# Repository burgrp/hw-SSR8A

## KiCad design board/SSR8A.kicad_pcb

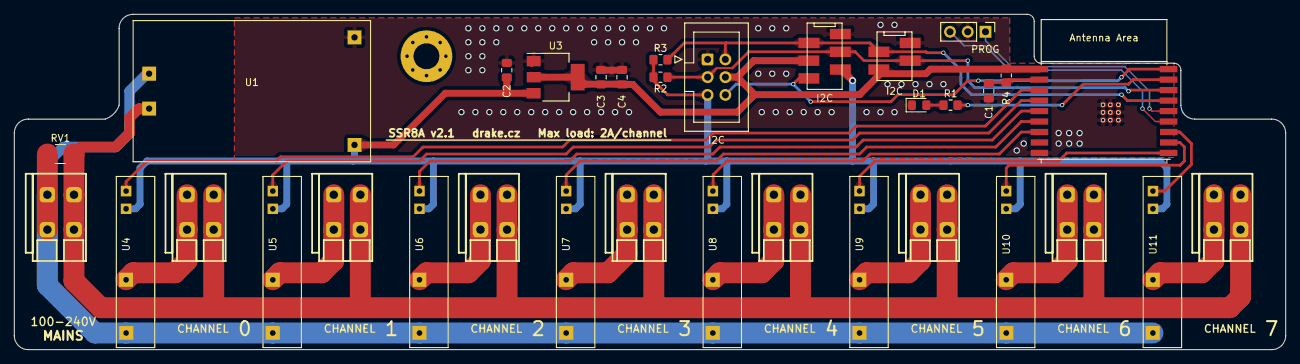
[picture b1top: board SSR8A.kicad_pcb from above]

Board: 2 copper layers, 182.0 x 48.0 mm, 35 parts (0 on the bottom side), 29 nets.

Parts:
C1: 1u; C_0805_2012Metric_Pad1.18x1.45mm_HandSolder
C2: 10u; C_0805_2012Metric_Pad1.18x1.45mm_HandSolder
C3, C4: 47u; C_0805_2012Metric_Pad1.18x1.45mm_HandSolder
D1: LED; LED_0805_2012Metric_Pad1.15x1.40mm_HandSolder
H1: MountingHole; MountingHole_3.7mm_Pad_Via
IN1: Conn_01x02; DG235-3.81-02P
J1: PROG; PinHeader_1x03_P2.54mm_Vertical
J2, J3, J4, J5, J6, J7, J8, J9: Conn_01x02; DG235-3.81-02P
R1: 270R; R_0805_2012Metric_Pad1.20x1.40mm_HandSolder
R2, R3: 4k7; R_0805_2012Metric_Pad1.20x1.40mm_HandSolder
R4: 10k; R_0805_2012Metric_Pad1.20x1.40mm_HandSolder
RV1: B72650M251K72; R_1210_3225Metric_Pad1.30x2.65mm_HandSolder
U1: HLK-PM01
U2: ESP32-C3-WROOM-02; ESP32-C3-WROOM-02 Handsolder
U3: LM1117-3.3; SOT-223-3_TabPin2
U4, U5, U6, U7, U8, U9, U10, U11: G3MB-SSR
X1: I2C; Micro-Match-FOB-4
X2: I2C; Micro-Match-FOB-6
X3: I2C; IDC-Header_2x03_P2.54mm_Vertical

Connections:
+3V3: C3.1, C4.1, R4.1, U2.1 (3V3), U3.2 (VO), X1.4 (3V3), X2.4 (3V3), X3.4 (3V3)
+5V: C2.1, R2.2, R3.1, U1.4 (OUT+), U3.3 (VI), U4.3 (IN+), U5.3 (IN+), U6.3 (IN+), U7.3 (IN+), U8.3 (IN+), U9.3 (IN+), U10.3 (IN+), U11.3 (IN+), X2.5 (5V), X3.5 (5V)
/ALERT: U2.18 (GPIO0/ADC1_CH0/XTAL_32K_P), X2.6 (ALERT), X3.6 (ALERT)
/LED: R1.2, U2.17 (GPIO1/ADC1_CH1/XTAL_32K_N)
/MAINS-L: IN1.1, RV1.1, U1.1 (LINE1), U4.1 (LOAD1), U5.1 (LOAD1), U6.1 (LOAD1), U7.1 (LOAD1), U8.1 (LOAD1), U9.1 (LOAD1), U10.1 (LOAD1), U11.1 (LOAD1)
/MAINS-N: IN1.2, J2.2, J3.2, J4.2, J5.2, J6.2, J7.2, J8.2, J9.2, RV1.2, U1.2 (LINE2)
/SCL: R3.2, U2.15 (GPIO3/ADC1_CH3), X1.2 (SCL), X2.2 (SCL), X3.2 (SCL)
/SDA: R2.1, U2.16 (GPIO2/ADC1_CH2), X1.3 (SDA), X2.3 (SDA), X3.3 (SDA)
/USB_D+: J1.1, U2.14 (GPIO19/USB_D+)
/USB_D-: J1.3, U2.13 (GPIO18/USB_D-)
//CH0: U2.3 (GPIO4/ADC1_CH4), U4.4 (IN-)
//CH1: U2.4 (GPIO5/ADC2_CH0), U5.4 (IN-)
//CH2: U2.5 (GPIO6), U6.4 (IN-)
//CH3: U2.6 (GPIO7), U7.4 (IN-)
//CH4: U2.7 (GPIO8), U8.4 (IN-)
//CH5: U2.10 (GPIO10), U9.4 (IN-)
//CH6: U2.11 (GPIO20/U0RXD), U10.4 (IN-)
//CH7: U2.12 (GPIO21/U0TXD), U11.4 (IN-)
GND: C1.2, C2.2, C3.2, C4.2, D1.1 (K), J1.2, U1.3 (OUT-), U2.9 (GND), U2.19 (GND), U3.1 (GND), X1.1 (GND), X2.1 (GND), X3.1 (GND)
unnamed: D1.2 (A), R1.1
unnamed: J2.1, U4.2 (LOAD2)
unnamed: J3.1, U5.2 (LOAD2)
unnamed: J4.1, U6.2 (LOAD2)
unnamed: J5.1, U7.2 (LOAD2)
unnamed: J6.1, U8.2 (LOAD2)
unnamed: J7.1, U9.2 (LOAD2)
unnamed: J8.1, U10.2 (LOAD2)
unnamed: J9.1, U11.2 (LOAD2)
unnamed: C1.1, R4.2, U2.2 (EN/CHIP_PU)

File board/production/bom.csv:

Designator,Footprint,Quantity,Value,LCSC Part #
C1,0805,1,1u,
C2,0805,1,10u,
C3,0805,1,47u,
C4,0805,1,47u,
D1,0805,1,LED,
H1,MountingHole_3.7mm_Pad_Via,1,MountingHole,
"IN1, J2, J3, J4, J5, J6, J7, J8, J9",DG235-3.81-02P,9,Conn_01x02,
J1,PinHeader_1x03_P2.54mm_Vertical,1,PROG,
R1,0805,1,270R,
R2,0805,1,4k7,
R3,0805,1,4k7,
R4,0805,1,10k,
RV1,1210,1,B72650M251K72,
U1,HLK-PM01,1,HLK-PM01,
"U10, U11, U4, U5, U6, U7, U8, U9",G3MB-SSR,8,G3MB-SSR,
U2,ESP32-C3-WROOM-02 Handsolder,1,ESP32-C3-WROOM-02,
U3,SOT-223-3_TabPin2,1,LM1117-3.3,
X1,Micro-Match-FOB-4,1,I2C,
X2,Micro-Match-FOB-6,1,I2C,
X3,IDC-Header_2x03_P2.54mm_Vertical,1,I2C,
